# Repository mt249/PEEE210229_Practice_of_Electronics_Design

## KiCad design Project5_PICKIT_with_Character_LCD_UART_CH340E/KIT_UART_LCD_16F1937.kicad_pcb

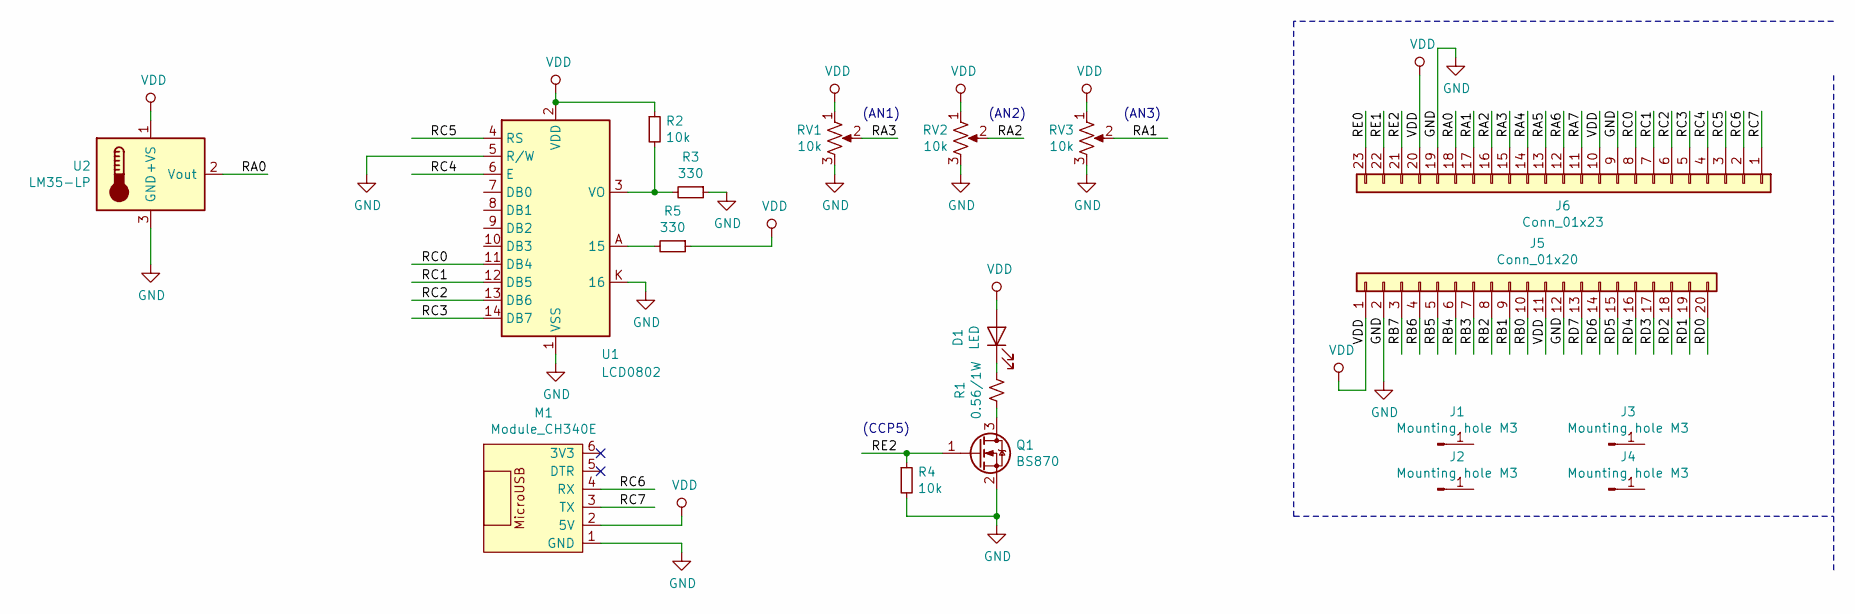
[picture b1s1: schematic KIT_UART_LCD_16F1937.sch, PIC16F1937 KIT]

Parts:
D1: LED; LED_1W_3W_R8
J1, J2, J3, J4: Mounting hole M3; MountingHole_2.5mm_Pad_Via
J5: Conn_01x20; PinHeader_1x20_P2.54mm_Vertical
J6: Conn_01x23; PinSocket_1x23_P2.54mm_Vertical
M1: Module_CH340E; Module CH340E mini
Q1: BS870; SOT-23
R1: 0.56/1W; R_Axial_DIN0414_L11.9mm_D4.5mm_P15.24mm_Horizontal
R2, R4: 10k; R_0805_2012Metric
R3, R5: 330; R_0805_2012Metric
RV1, RV2, RV3: 10k; Potentiometer_Alpha_RD901F-40-00D_Single_Vertical
U1: LCD0802; LCD_0802
U2: LM35-LP; TO-92_Inline_W4.0mm_Horizontal_FlatSideDown

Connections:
/RA0: J6.18, U2.2 (Vout)
/RA1: J6.17, RV3.2
/RA2: J6.16, RV2.2
/RA3: J6.15, RV1.2
/RA4: J6.14
/RA5: J6.13
/RA6: J6.12
/RA7: J6.11
/RB0: J5.10
/RB1: J5.9
/RB2: J5.8
/RB3: J5.7
/RB4: J5.6
/RB5: J5.5
/RB6: J5.4
/RB7: J5.3
/RC0: J6.8, U1.11 (DB4)
/RC1: J6.7, U1.12 (DB5)
/RC2: J6.6, U1.13 (DB6)
/RC3: J6.5, U1.14 (DB7)
/RC4: J6.4, U1.6 (E)
/RC5: J6.3, U1.4 (RS)
/RC6: J6.2, M1.4 (RX)
/RC7: J6.1, M1.3 (TX)
/RD0: J5.20
/RD1: J5.19
/RD2: J5.18
/RD3: J5.17
/RD4: J5.16
/RD5: J5.15
/RD6: J5.14
/RD7: J5.13
/RE0: J6.23
/RE1: J6.22
/RE2: J6.21, Q1.1 (G), R4.1
GND: J5.2, J5.12, J6.9, J6.19, M1.1 (GND), Q1.2 (S), R3.1, R4.2, RV1.3, RV2.3, RV3.3, U1.1 (VSS), U1.5 (R/W), U1.16, U1.K (16), U2.3 (GND)
unnamed: D1.1 (K), R1.1
unnamed: Q1.3 (D), R1.2
unnamed: R2.2, R3.2, U1.3 (VO)
unnamed: R5.2, U1.15, U1.A (15)
VDD: D1.2 (A), J5.1, J5.11, J6.10, J6.20, M1.2 (5V), R2.1, R5.1, RV1.1, RV2.1, RV3.1, U1.2 (VDD), U2.1 (+VS)

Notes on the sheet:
(CCP5)
(AN1)
(AN2)
(AN3)

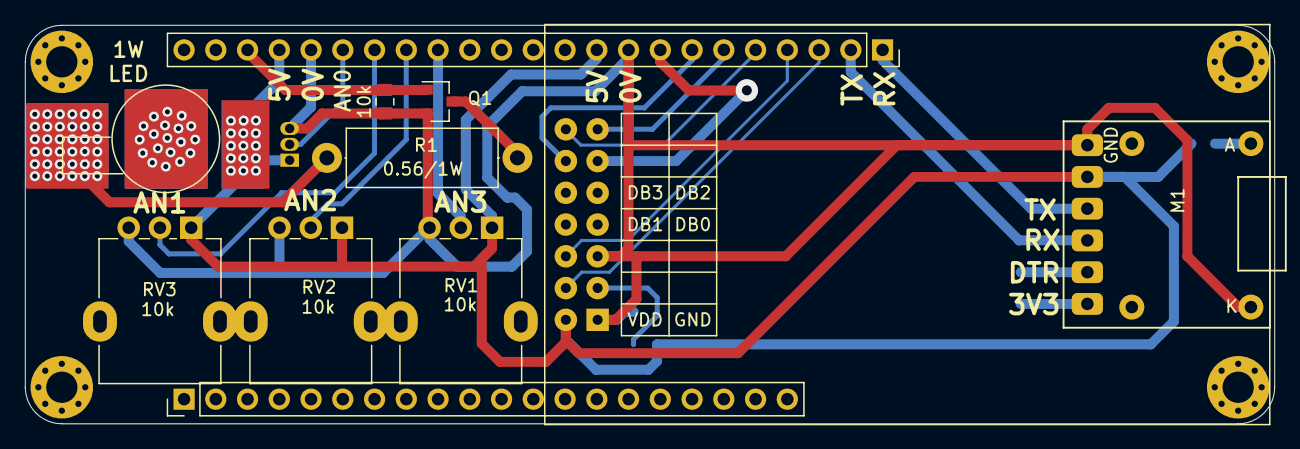
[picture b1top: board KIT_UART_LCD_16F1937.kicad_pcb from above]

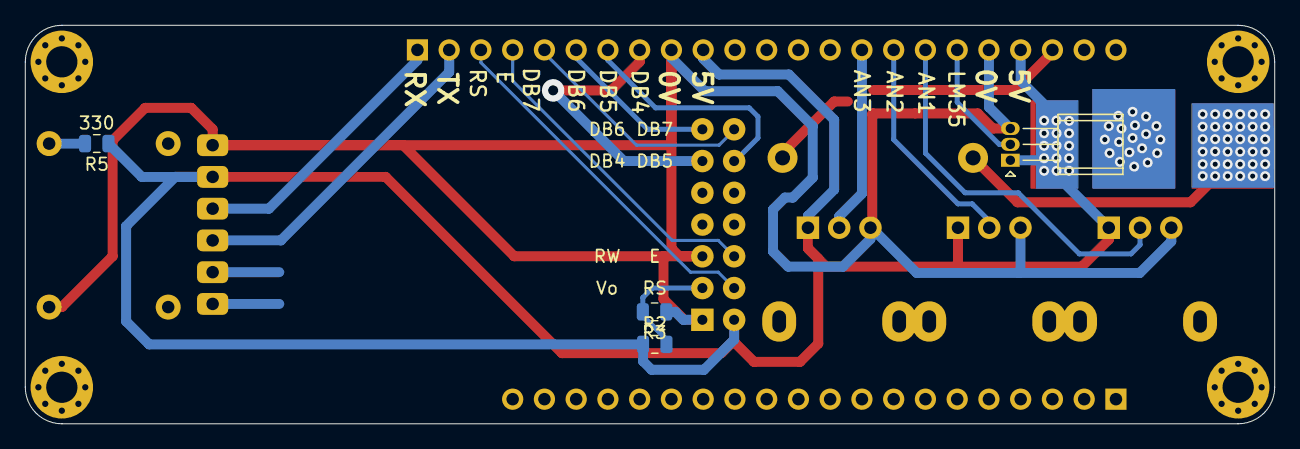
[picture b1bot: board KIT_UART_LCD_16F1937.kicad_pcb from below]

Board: 2 copper layers, 99.9 x 31.9 mm, 19 parts (4 on the bottom side), 19 nets.

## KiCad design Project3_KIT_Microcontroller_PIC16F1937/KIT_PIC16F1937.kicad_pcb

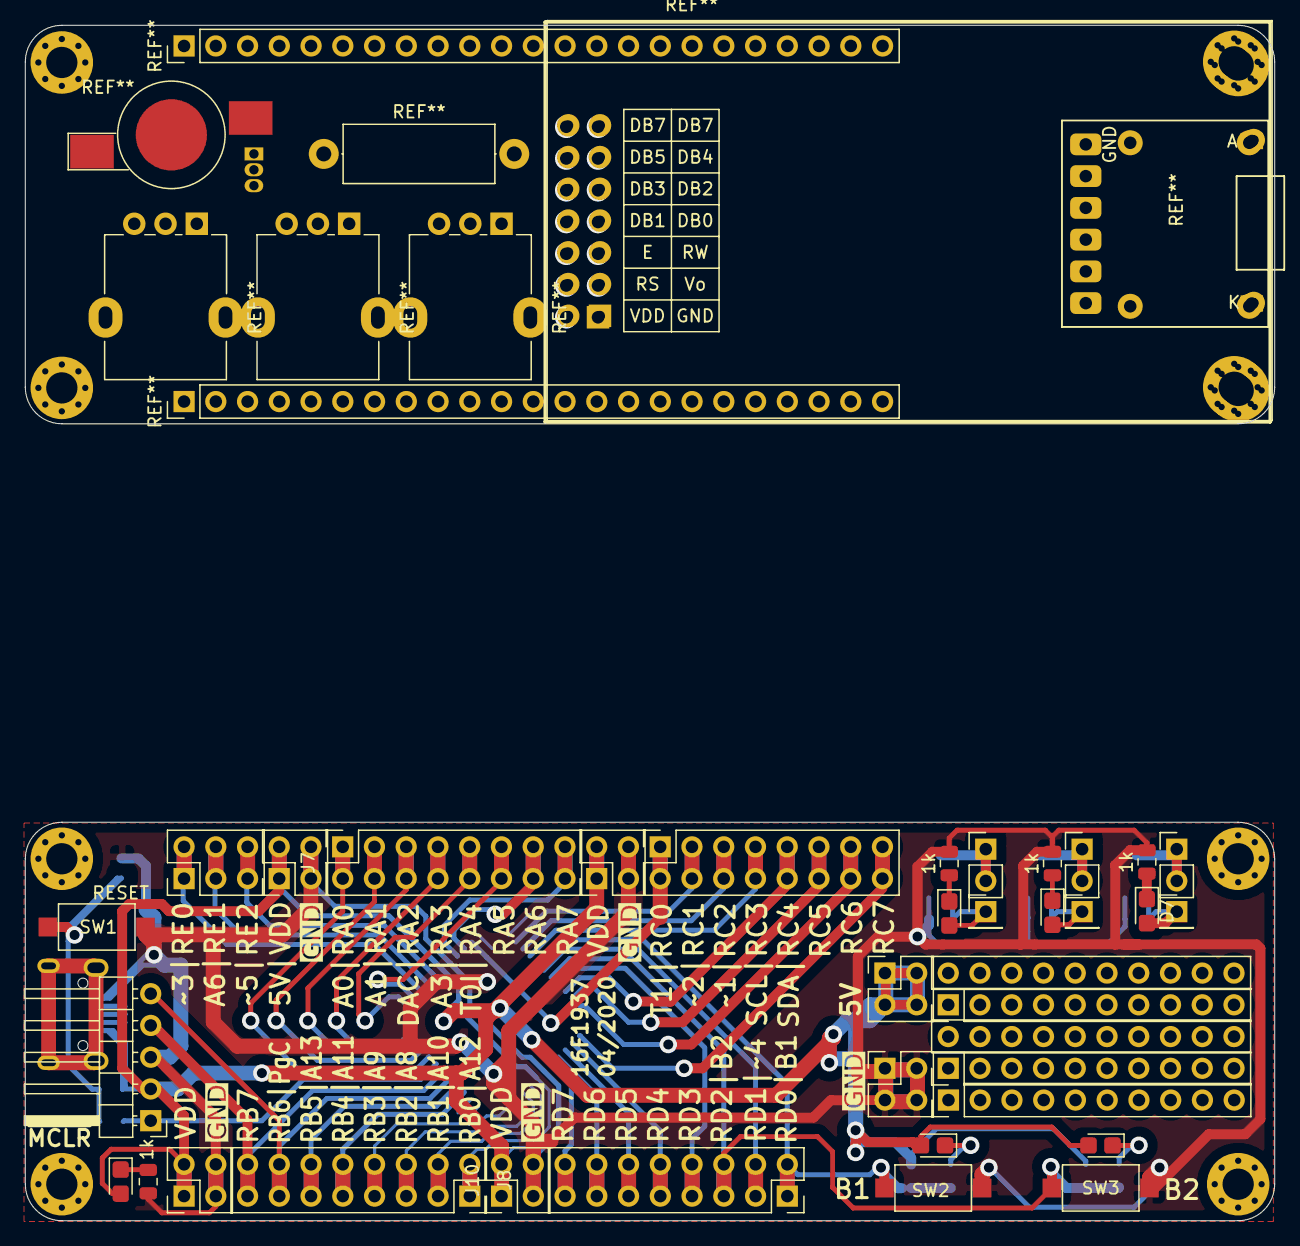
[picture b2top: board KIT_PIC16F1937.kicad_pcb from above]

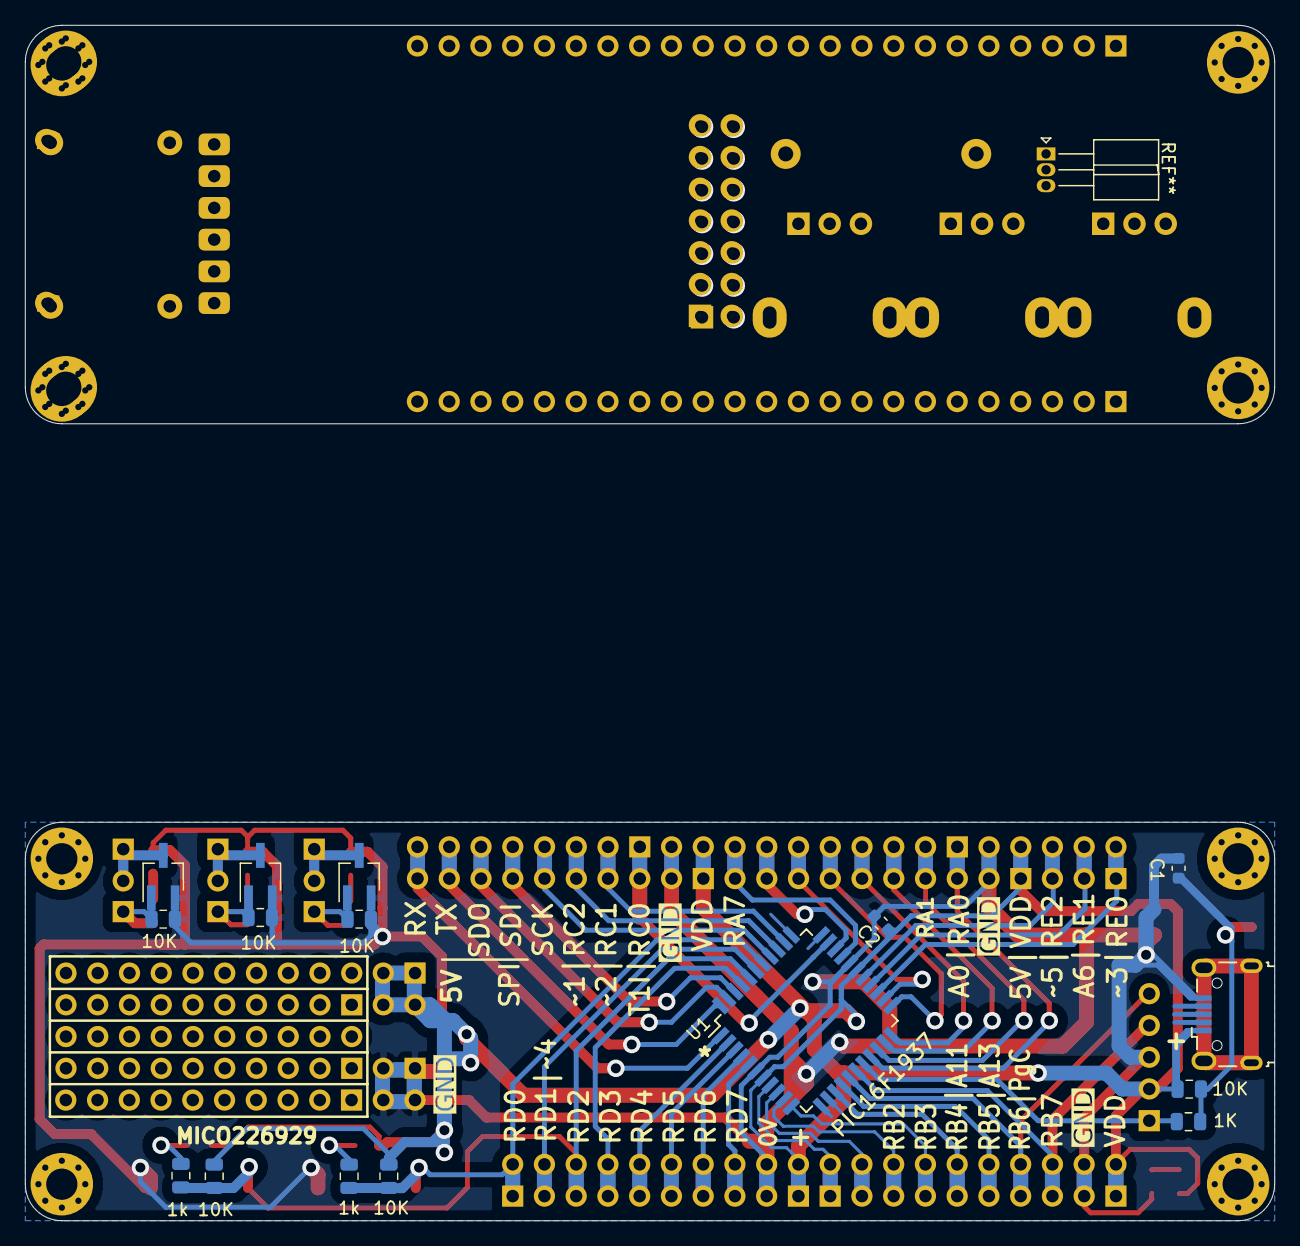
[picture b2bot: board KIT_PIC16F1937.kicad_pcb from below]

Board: 2 copper layers, 99.9 x 95.6 mm, 60 parts (16 on the bottom side), 55 nets.

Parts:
C1, C2: 0.1uF; C_0603_1608Metric
D1: PWR; LED_0805_2012Metric_Castellated
D2, D3, D5, D6, D7: LED; LED_0805_2012Metric_Castellated
J1, J1#2, J2, J2#2, J3, J3#2, J3#3, J4, J4#2, J4#3: Mounting hole M3; MountingHole_2.5mm_Pad_Via
J5: PORTC; PinSocket_2x08_P2.54mm_Vertical
J6: PORTD; PinSocket_2x08_P2.54mm_Vertical
J7: PORTA; PinSocket_2x08_P2.54mm_Vertical
J8: PORTB; PinSocket_2x08_P2.54mm_Vertical
J9: ISP; PinHeader_1x05_P2.54mm_Horizontal
J10, J11, J12, J13, J25, J26: PWR; PinHeader_2x02_P2.54mm_Vertical
J14: PORTE; PinHeader_2x03_P2.54mm_Vertical
J15, J18, J20: LOAD; PinHeader_1x02_P2.54mm_Vertical
J16, J17, J19: FET; PinHeader_1x01_P2.54mm_Vertical
J21, J22: PAD; PinHeader_2x10_P2.54mm_Vertical
J23: Conn_01x10; PinHeader_1x10_P2.54mm_Vertical
J24: USB_B_Micro; USB_Micro-B_Wuerth_629105150521
Q1, Q2, Q3: BS870; SOT-23W_Handsoldering
R1: 1K; R_0805_2012Metric
R2, R5, R7, R8, R9, R10: 10K; R_0805_2012Metric
R3, R4, R6, R12, R13, R14: 1k; R_0805_2012Metric
SW1: RESET; SW_SPST_CK_RS282G05A3
SW2: B1; SW_SPST_CK_RS282G05A3
SW3: B2; SW_SPST_CK_RS282G05A3
U1: PIC16F1937-IPT; TQFP-44_10x10mm_P0.8mm

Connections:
/RA0: J7.1, J7.2, U1.19
/RA1: J7.3, J7.4, U1.20
/RA2: J7.5, J7.6, U1.21
/RA3: J7.7, J7.8, U1.22
/RA4: J7.9, J7.10, U1.23
/RA5: J7.11, J7.12, U1.24
/RA6: J7.13, J7.14, U1.31
/RA7: J7.15, J7.16, U1.30
/RB0: J8.1, J8.2, U1.8
/RB1: J8.3, J8.4, U1.9
/RB2: J8.5, J8.6, U1.10
/RB3: J8.7, J8.8, U1.11
/RB4: J8.9, J8.10, U1.14
/RB5: J8.11, J8.12, U1.15
/RB6: J8.13, J8.14, J9.5, U1.16
/RB7: J8.15, J8.16, J9.4, U1.17
/RC0: J5.1, J5.2, U1.32
/RC1: J5.3, J5.4, U1.35
/RC2: J5.5, J5.6, U1.36
/RC3: J5.7, J5.8, U1.37
/RC4: J5.9, J5.10, U1.42
/RC5: J5.11, J5.12, U1.43
/RC6: J5.13, J5.14, U1.44
/RC7: J5.15, J5.16, U1.1
/RD0: J6.1, J6.2, R4.1, R5.1, SW2.1, U1.38
/RD1: J6.3, J6.4, U1.39
/RD2: J6.5, J6.6, R6.1, R7.1, SW3.1, U1.40
/RD3: J6.7, J6.8, U1.41
/RD4: J6.9, J6.10, U1.2
/RD5: J6.11, J6.12, U1.3
/RD6: J6.13, J6.14, U1.4
/RD7: J6.15, J6.16, U1.5
/RE0: J14.1, J14.2, U1.25
/RE1: J14.3, J14.4, U1.26
/RE2: J14.5, J14.6, U1.27
/~MCLR~: J9.1, R1.2, U1.18
GND: C1.2, C2.2, J9.3, J10.3, J10.4, J11.3, J11.4, J12.3, J12.4, J13.3, J13.4, J24.5, J26.1, J26.2, J26.3, J26.4, Q1.2, Q2.2, Q3.2, R3.1, R8.1, R9.1, R10.1, R12.1, R13.1, R14.1, SW1.2, SW2.2, SW3.2, U1.6, U1.29
unnamed: C1.1, R1.1, R2.1, SW1.1
unnamed: D1.1, R3.2
unnamed: D2.1, R4.2
unnamed: D3.1, R6.2
unnamed: D5.1, R12.2
unnamed: D5.2, J16.1, Q1.1, R8.2
unnamed: D6.1, R13.2
unnamed: D6.2, J17.1, Q2.1, R9.2
unnamed: D7.1, R14.2
unnamed: D7.2, J19.1, Q3.1, R10.2
unnamed: J1.1, J1#2.1
unnamed: J2.1, J2#2.1
unnamed: J3.1, J3#2.1, J3#3.1
unnamed: J4.1, J4#2.1, J4#3.1
unnamed: J15.1, J15.2, Q1.3
unnamed: J18.1, J18.2, Q2.3
unnamed: J20.1, J20.2, Q3.3
VDD: C2.1, D1.2, D2.2, D3.2, J9.2, J10.1, J10.2, J11.1, J11.2, J12.1, J12.2, J13.1, J13.2, J24.1, J25.1, J25.2, J25.3, J25.4, R2.2, R5.2, R7.2, U1.7, U1.28

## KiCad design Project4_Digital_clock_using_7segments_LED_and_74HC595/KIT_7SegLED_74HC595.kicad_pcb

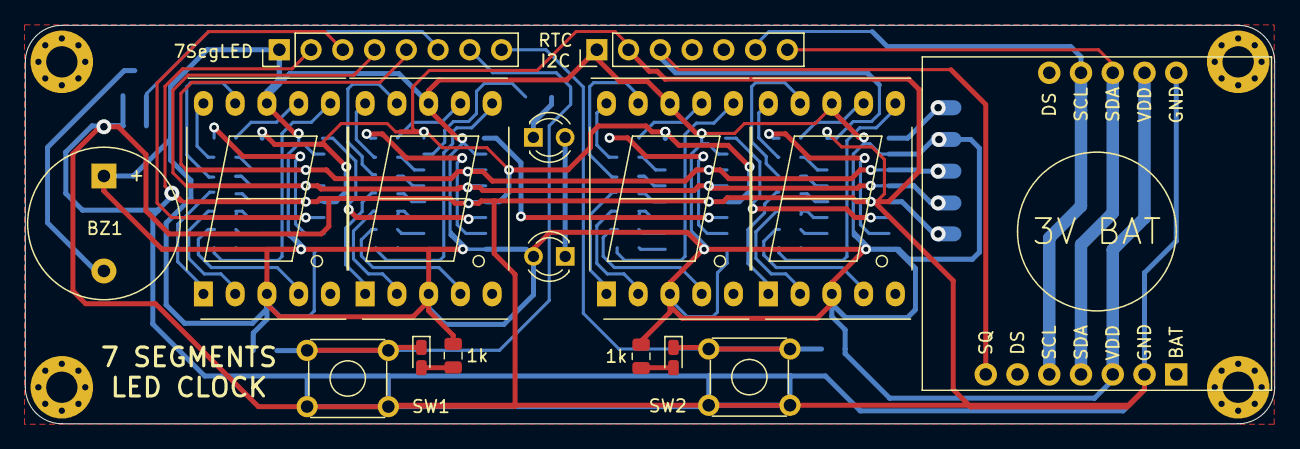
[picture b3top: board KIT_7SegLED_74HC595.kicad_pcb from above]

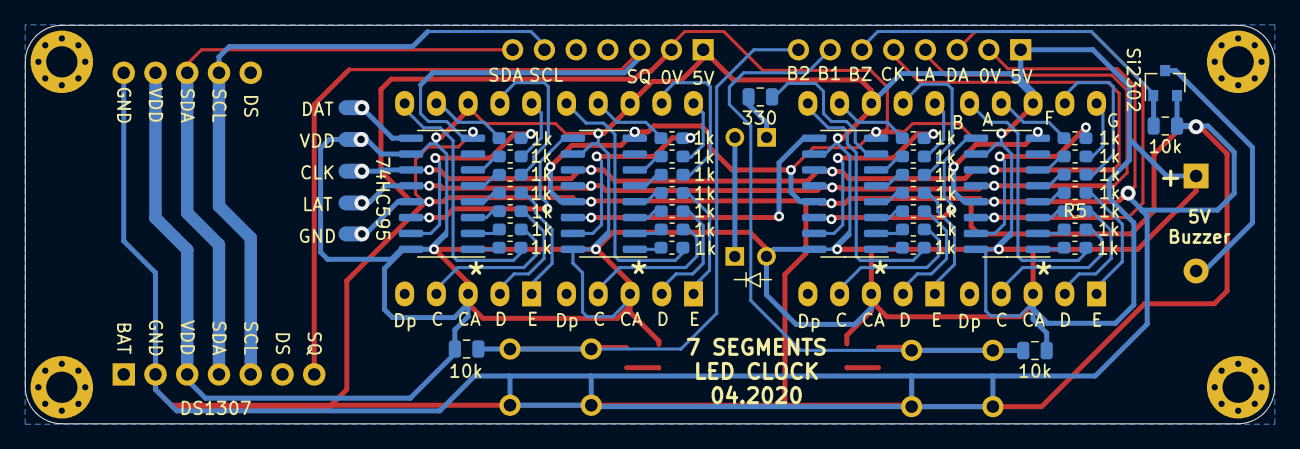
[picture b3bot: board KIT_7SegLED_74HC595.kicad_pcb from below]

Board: 2 copper layers, 99.9 x 31.9 mm, 57 parts (37 on the bottom side), 75 nets.

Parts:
BZ1: Buzzer; Buzzer_12x9.5RM7.6
D1: DOT1; LED_D3.0mm
D2: DOT2; LED_D3.0mm
D3, D4: D1; LED_0603_1608Metric_Castellated
J1, J2#2, J3, J4: Mounting hole M3; MountingHole_2.5mm_Pad_Via
J1#2: LED_CON; PinHeader_1x08_P2.54mm_Vertical
J2: Conn_01x07; PinHeader_1x07_P2.54mm_Vertical
Q1: Si2302; SOT-23
R1, R2, R3, R4, R5, R6, R7, R9, R10, R11, R12, R13, R14, R15, R17, R18, R19, R20, R21, R22, R23, R25, R26, R27, R28, R29, R30, R31: 1k; R_0603_1608Metric_Pad1.05x0.95mm_HandSolder
R8: 330; R_0805_2012Metric
R16, R24, R32: 10k; R_0805_2012Metric
R33, R34: 1k; R_0805_2012Metric
SW1, SW2: SW1; SW_TH_Tactile_Omron_B3F-10xx
U1, U3, U5, U7: 74HC595; SOIC-16_3.9x9.9mm_P1.27mm
U2, U4, U6, U8: KCSA02-105; 7SegmentLED_LTS6760_LTS6780
U9: Tiny_RTC_DS1307; Tiny RTC DS1307

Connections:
/B1: D3.1, J1#2.7, R16.1, SW1.1, SW1.2
/B2: D4.1, J1#2.8, R24.1, SW2.1, SW2.2
/BUZZ: J1#2.6, Q1.1, R32.1
/CLK: J1#2.5, U1.11, U3.11, U5.11, U7.11
/DAT: J1#2.3, U1.14
/LAT: J1#2.4, U1.12, U3.12, U5.12, U7.12
/SCL: J2.6, U9.5, U9.11
/SDA: J2.7, U9.4, U9.10
/SQ: J1#2.2, J2.2, J2.3, Q1.2, R32.2, SW1.3, SW1.4, SW2.3, SW2.4, U1.8, U1.13, U3.8, U3.13, U5.8, U5.13, U7.8, U7.13, U9.2, U9.7, U9.8
/sheet5E8DD3E7/DATA_IN: U1.9, U3.14
/sheet5E8DD3E7/DOTLED: R8.1, U3.7
/sheet5E8DD7BC/DATA_IN: U3.9, U5.14
/sheet5E8DDA44/DATA_IN: U5.9, U7.14
unnamed: BZ1.2, Q1.3
unnamed: D1.1, R8.2
unnamed: D1.2, D2.1
unnamed: D3.2, R33.1
unnamed: D4.2, R34.1
unnamed: R1.1, U2.7
unnamed: R1.2, U1.15
unnamed: R2.1, U2.6
unnamed: R2.2, U1.1
unnamed: R3.1, U2.4
unnamed: R3.2, U1.2
unnamed: R4.1, U2.2
unnamed: R4.2, U1.3
unnamed: R5.1, U2.1
unnamed: R5.2, U1.4
unnamed: R6.1, U2.9
unnamed: R6.2, U1.5
unnamed: R7.1, U2.10
unnamed: R7.2, U1.6
unnamed: R9.1, U4.7
unnamed: R9.2, U3.15
unnamed: R10.1, U4.6
unnamed: R10.2, U3.1
unnamed: R11.1, U4.4
unnamed: R11.2, U3.2
unnamed: R12.1, U4.2
unnamed: R12.2, U3.3
unnamed: R13.1, U4.1
unnamed: R13.2, U3.4
unnamed: R14.1, U4.9
unnamed: R14.2, U3.5
unnamed: R15.1, U4.10
unnamed: R15.2, U3.6
unnamed: R17.1, U6.7
unnamed: R17.2, U5.15
unnamed: R18.1, U6.6
unnamed: R18.2, U5.1
unnamed: R19.1, U6.4
unnamed: R19.2, U5.2
unnamed: R20.1, U6.2
unnamed: R20.2, U5.3
unnamed: R21.1, U6.1
unnamed: R21.2, U5.4
unnamed: R22.1, U6.9
unnamed: R22.2, U5.5
unnamed: R23.1, U6.10
unnamed: R23.2, U5.6
unnamed: R25.1, U8.7
unnamed: R25.2, U7.15
unnamed: R26.1, U8.6
unnamed: R26.2, U7.1
unnamed: R27.1, U8.4
unnamed: R27.2, U7.2
unnamed: R28.1, U8.2
unnamed: R28.2, U7.3
unnamed: R29.1, U8.1
unnamed: R29.2, U7.4
unnamed: R30.1, U8.9
unnamed: R30.2, U7.5
unnamed: R31.1, U8.10
unnamed: R31.2, U7.6
VDD: BZ1.1, D2.2, J1#2.1, J2.1, R16.2, R24.2, R33.2, R34.2, U1.10, U1.16, U2.3, U2.8, U3.10, U3.16, U4.3, U4.8, U5.10, U5.16, U6.3, U6.8, U7.10, U7.16, U8.3, U8.8, U9.3, U9.9

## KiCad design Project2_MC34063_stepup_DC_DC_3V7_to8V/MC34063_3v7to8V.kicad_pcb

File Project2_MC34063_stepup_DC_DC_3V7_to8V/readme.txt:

Các bạn xem video ở đây
https://www.youtube.com/watch?v=uYEVXo8IzLs&list=PLLb0wIuhHnH22__SY4lo0tVAaMEDcjebu&index=2

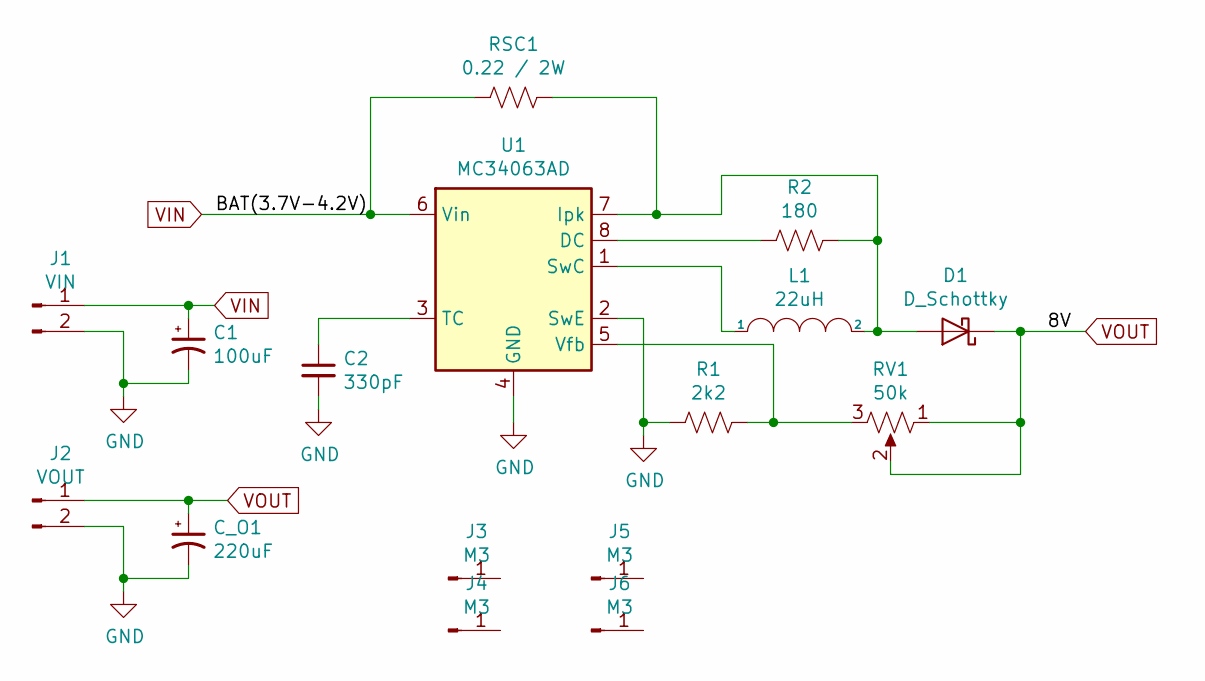
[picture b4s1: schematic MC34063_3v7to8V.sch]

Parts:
C1: 100uF; CP_Radial_D8.0mm_P5.00mm
C2: 330pF; C_0805_2012Metric_Pad1.15x1.40mm_HandSolder
C_O1: 220uF; CP_Radial_D8.0mm_P5.00mm
D1: D_Schottky; D_SMB_Handsoldering
J1: VIN; PinHeader_1x02_P2.54mm_Vertical
J2: VOUT; PinHeader_1x02_P2.54mm_Vertical
J3, J4, J5, J6: M3; MountingHole_2.5mm_Pad
L1: 22uH; Inductor_
R1: 2k2; R_0805_HandSoldering
R2: 180; R_0805_HandSoldering
RSC1: 0.22 / 2W; R_Axial_DIN0207_L6.3mm_D2.5mm_P15.24mm_Horizontal
RV1: 50k; Potentiometer_Bourns_3266Y_Vertical
U1: MC34063AD; SOIC-8_3.9x4.9mm_P1.27mm

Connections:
GND: C1.2, C2.2, C_O1.2, J1.2, J2.2, R1.2, U1.2 (SwE), U1.4 (GND)
unnamed: C2.1, U1.3 (TC)
unnamed: D1.2 (A), L1.2, R2.1, RSC1.1, U1.7 (Ipk)
unnamed: L1.1, U1.1 (SwC)
unnamed: R1.1, RV1.3, U1.5 (Vfb)
unnamed: R2.2, U1.8 (DC)
VIN: C1.1, J1.1, RSC1.2, U1.6 (Vin)
VOUT: C_O1.1, D1.1 (K), J2.1, RV1.1, RV1.2

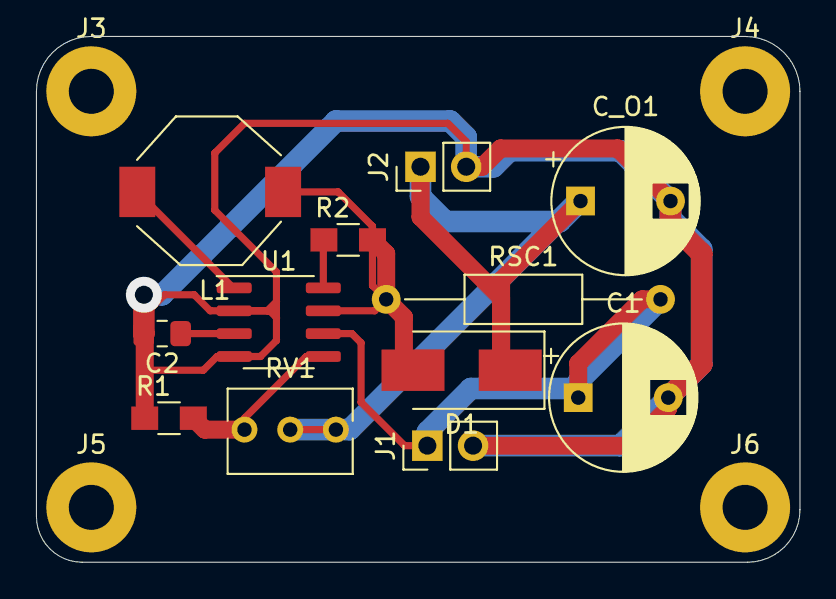
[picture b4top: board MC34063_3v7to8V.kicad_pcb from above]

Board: 2 copper layers, 42.4 x 29.2 mm, 16 parts (0 on the bottom side), 8 nets.

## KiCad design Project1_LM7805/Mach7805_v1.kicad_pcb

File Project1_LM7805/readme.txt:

Xem video huong dan thiet ke:
https://www.youtube.com/watch?v=CJteI1jn9hg&list=PLLb0wIuhHnH22__SY4lo0tVAaMEDcjebu&index=1

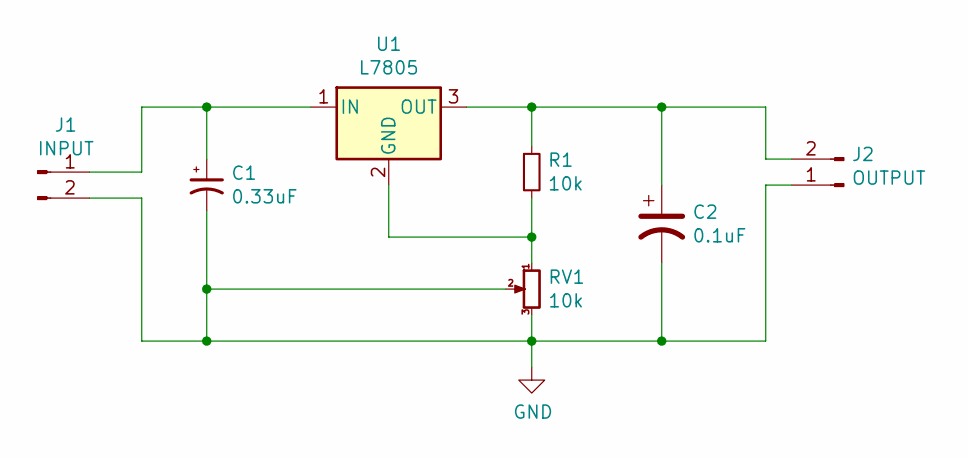
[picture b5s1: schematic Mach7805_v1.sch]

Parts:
C1: 0.33uF; CP_Radial_D5.0mm_P2.00mm
C2: 0.1uF; CP_Radial_D5.0mm_P2.00mm
J1: INPUT; PinHeader_1x02_P2.54mm_Vertical
J2: OUTPUT; PinHeader_1x02_P2.54mm_Vertical
R1: 10k; R_Axial_DIN0207_L6.3mm_D2.5mm_P10.16mm_Horizontal
RV1: 10k; Potentiometer_Piher_T-16H_Single_Horizontal
U1: L7805; TO-220-3_Horizontal_TabDown

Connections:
GND: C1.2, C2.2, J1.2, J2.1, RV1.2, RV1.3
unnamed: C1.1, J1.1, U1.1 (IN)
unnamed: C2.1, J2.2, R1.1, U1.3 (OUT)
unnamed: R1.2, RV1.1, U1.2 (GND)

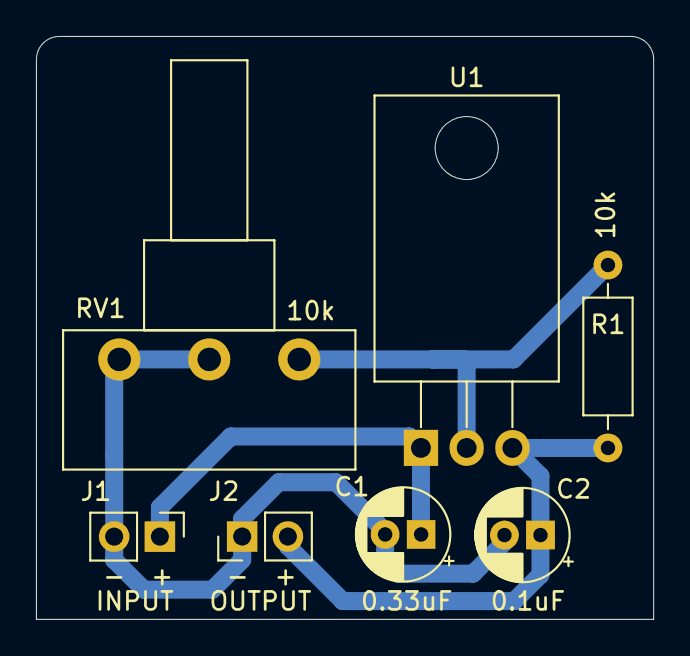
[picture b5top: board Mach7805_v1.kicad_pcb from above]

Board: 2 copper layers, 34.3 x 32.4 mm, 7 parts (0 on the bottom side), 4 nets.

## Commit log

2020-05-08 Rename readme.txt to readme.md
